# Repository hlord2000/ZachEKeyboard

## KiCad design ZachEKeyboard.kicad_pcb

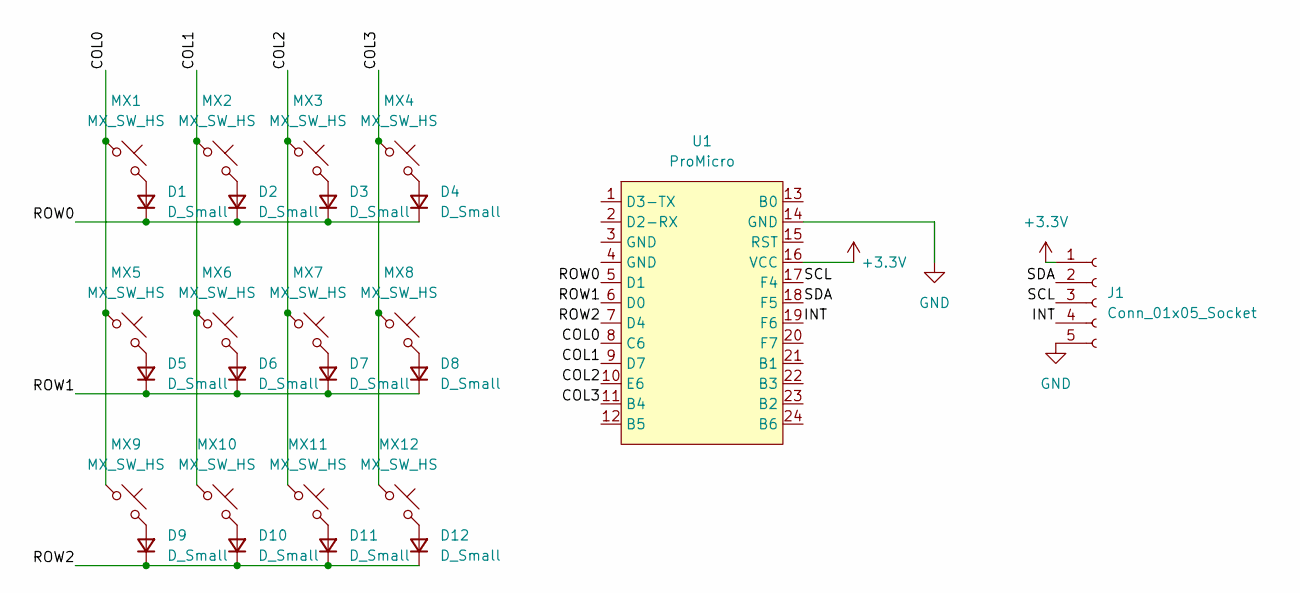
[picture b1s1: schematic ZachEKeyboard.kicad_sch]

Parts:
D1, D2, D3, D4, D5, D6, D7, D8, D9, D10, D11, D12: D_Small; D_SOD-123
J1: Conn_01x05_Socket; PinSocket_1x05_P2.54mm_Vertical
MX1, MX2, MX3, MX4, MX5, MX6, MX7, MX8, MX9, MX10, MX11, MX12: MX_SW_HS; SW_MX_HS_1u
U1: ProMicro; ProMicro_USBup

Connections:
+3.3V: J1.1, U1.16 (VCC)
/COL0: MX1.1, MX5.1, MX9.1, U1.8 (C6)
/COL1: MX2.1, MX6.1, MX10.1, U1.9 (D7)
/COL2: MX3.1, MX7.1, MX11.1, U1.10 (E6)
/COL3: MX4.1, MX8.1, MX12.1, U1.11 (B4)
/INT: J1.4, U1.19 (F6)
/ROW0: D1.1 (K), D2.1 (K), D3.1 (K), D4.1 (K), U1.5 (D1)
/ROW1: D5.1 (K), D6.1 (K), D7.1 (K), D8.1 (K), U1.6 (D0)
/ROW2: D9.1 (K), D10.1 (K), D11.1 (K), D12.1 (K), U1.7 (D4)
/SCL: J1.3, U1.17 (F4)
/SDA: J1.2, U1.18 (F5)
GND: J1.5, U1.14 (GND)
unnamed: D1.2 (A), MX1.2
unnamed: D2.2 (A), MX2.2
unnamed: D3.2 (A), MX3.2
unnamed: D4.2 (A), MX4.2
unnamed: D5.2 (A), MX5.2
unnamed: D6.2 (A), MX6.2
unnamed: D7.2 (A), MX7.2
unnamed: D8.2 (A), MX8.2
unnamed: D9.2 (A), MX9.2
unnamed: D10.2 (A), MX10.2
unnamed: D11.2 (A), MX11.2
unnamed: D12.2 (A), MX12.2

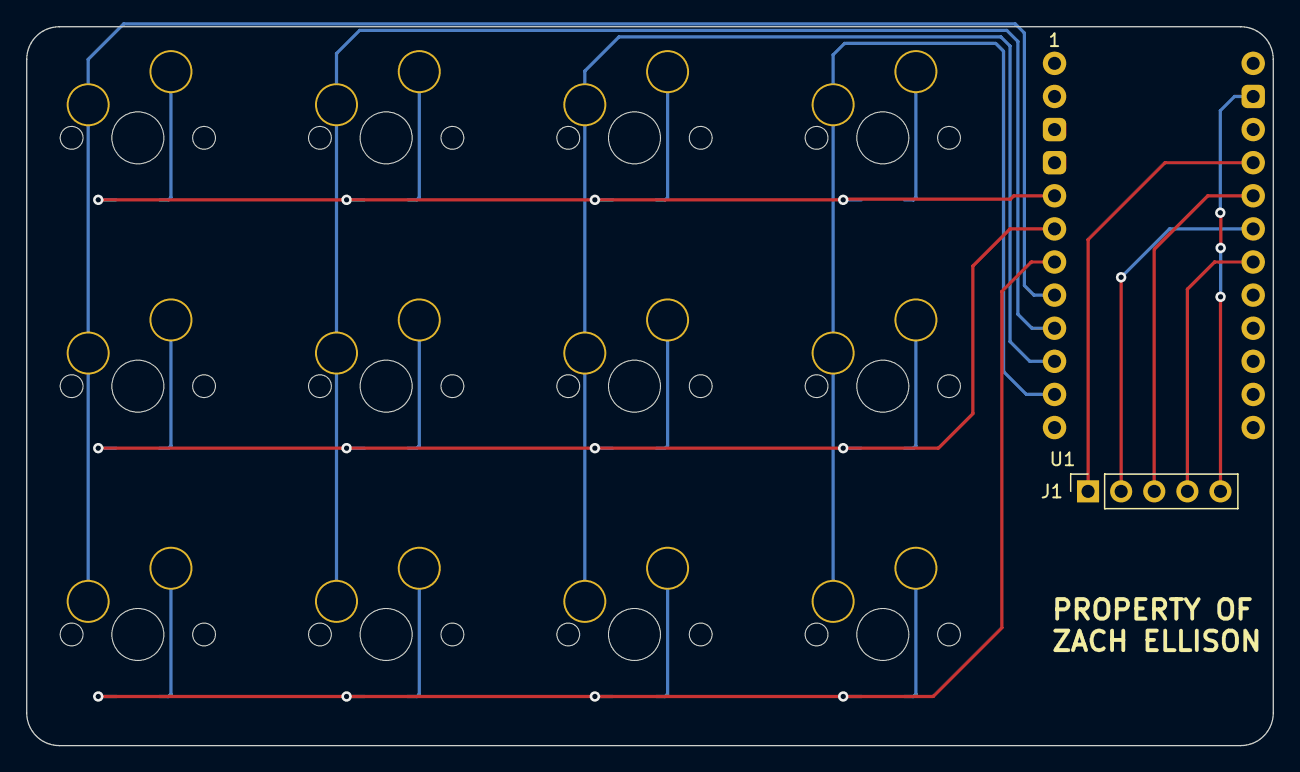
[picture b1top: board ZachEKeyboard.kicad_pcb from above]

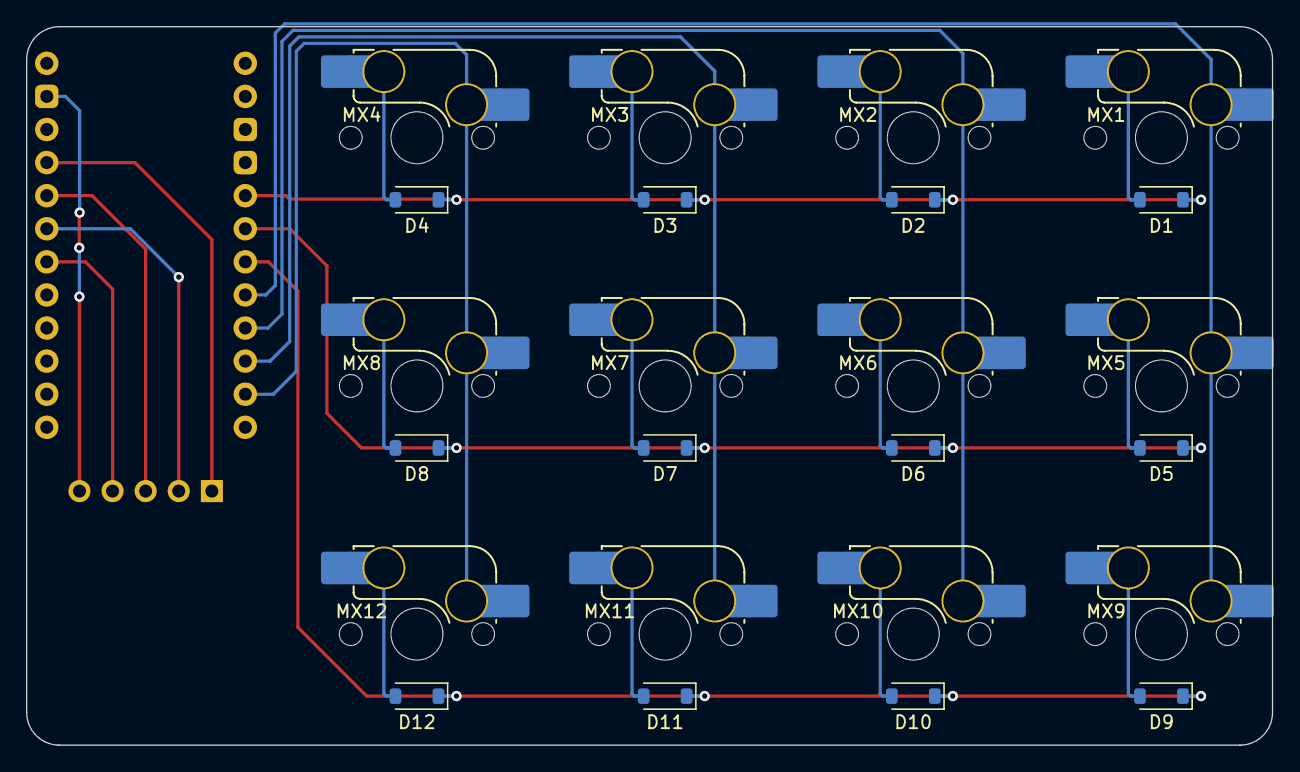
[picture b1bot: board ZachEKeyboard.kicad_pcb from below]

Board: 2 copper layers, 95.6 x 55.2 mm, 26 parts (24 on the bottom side), 24 nets.

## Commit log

2023-09-18 Initial commit.
2023-09-18 Fixed pinout
